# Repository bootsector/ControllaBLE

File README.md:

**ControllaBLE - A retro-controllers to Bluetooth BLE adapter**

This is an ESP32 based controller adapter that outputs as a dual joypad through
Bluetooth (BLE).

This was created using VSCode + PlatformIO extension.

ESP32 Arduino framework was used, along with the NimBLE Arduino library.

[This is the ESP32-WROOM-32 dev board](https://www.amazon.com/VKLSVAN-ESP-WROOM-32-Development-Dual-Mode-Microcontroller/dp/B07T6J3PXZ/ref=sr_1_21) you'll need to run this adapter.

For now it supports only up to 2 SNES controllers connected as:

- SNES pad (both) CLOCK Arduino pin: 19
- SNES pad (both) LATCH Arduino pin: 21
- SNES pad P1 DATA Arduino pin: 22
- SNES pad P2 DATA Arduino pin: 23

Support for more controllers will be added soon!

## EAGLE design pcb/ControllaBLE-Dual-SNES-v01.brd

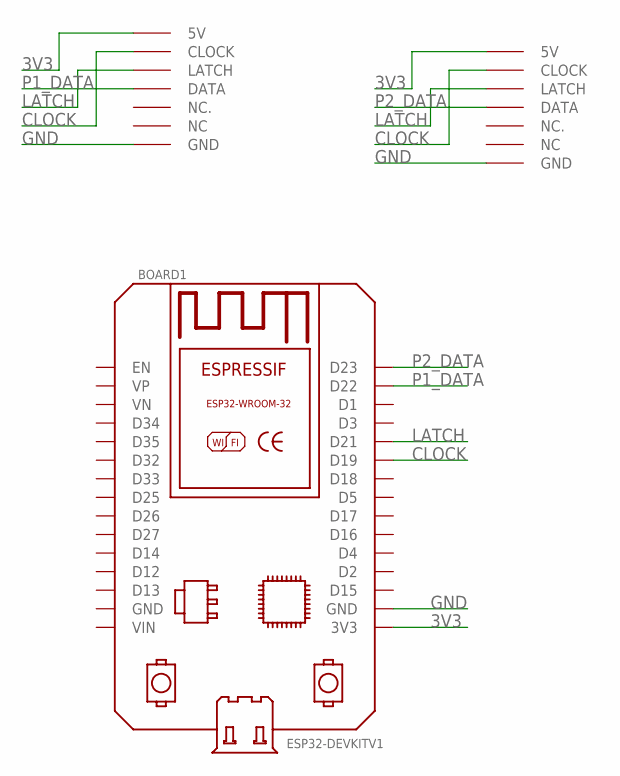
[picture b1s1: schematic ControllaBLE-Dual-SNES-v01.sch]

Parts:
BOARD1: ESP32DEVKITV1; ESP32-DEVKITV1
U$1, U$2: SNESCONN

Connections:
3V3: BOARD1.3V3, U$1.5V, U$2.5V
CLOCK: BOARD1.D19, U$1.CLOCK, U$2.CLOCK
GND: BOARD1.GND@1 (GND), U$1.GND, U$2.GND
LATCH: BOARD1.D21, U$1.LATCH, U$2.LATCH
P1_DATA: BOARD1.D22, U$1.DATA
P2_DATA: BOARD1.D23, U$2.DATA

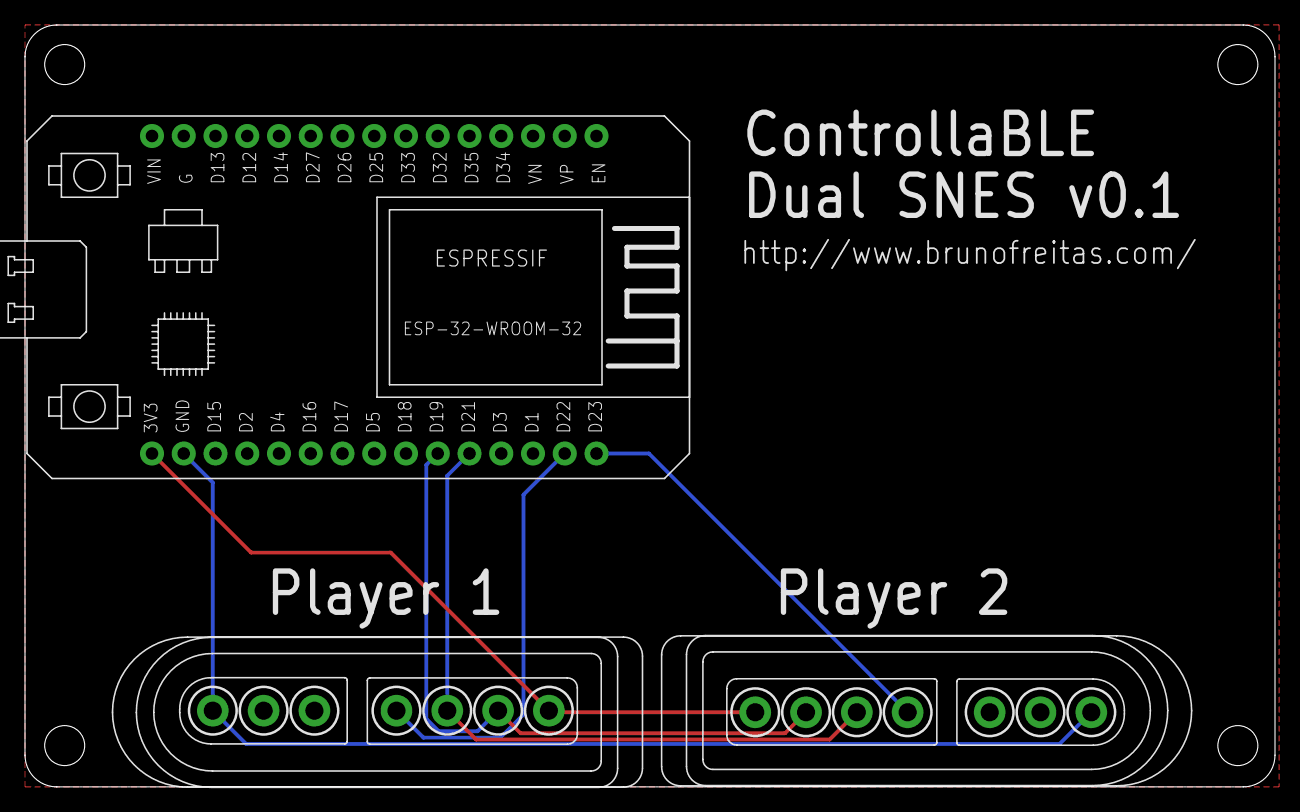
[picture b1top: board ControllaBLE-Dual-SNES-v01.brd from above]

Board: 2 copper layers, 100.0 x 61.0 mm, 3 parts (0 on the bottom side), 6 nets.

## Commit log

2021-09-03 Changed name to ControlaBLE (thanks, Rysha). Adding SNES input support for some tests
2021-09-03 Fixed wrong button reporting and avoiding spamming BLE
2021-09-03 Adding license
2021-09-03 Adding README
2021-09-03 Fix README
2021-09-04 Project name had a typo. Fixing it.
2021-09-04 Changing default connection params in an attempt to decrease latency
2021-09-04 1P only version for tests
2021-09-04 Led blinks when not paired. Stays lit when connected/paired.
2021-09-05 Adding Dual SNES v0.1 PCB files
2021-09-06 Changing VID:PID as per new pidcodes request (pending): https://github.com/pidcodes/pidcodes.github.com/pull/678
2021-09-20 Fixing wrong SNES connector position in the PCB
